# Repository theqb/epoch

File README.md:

# epoch
Open-source hardware + software lap-timer for racing

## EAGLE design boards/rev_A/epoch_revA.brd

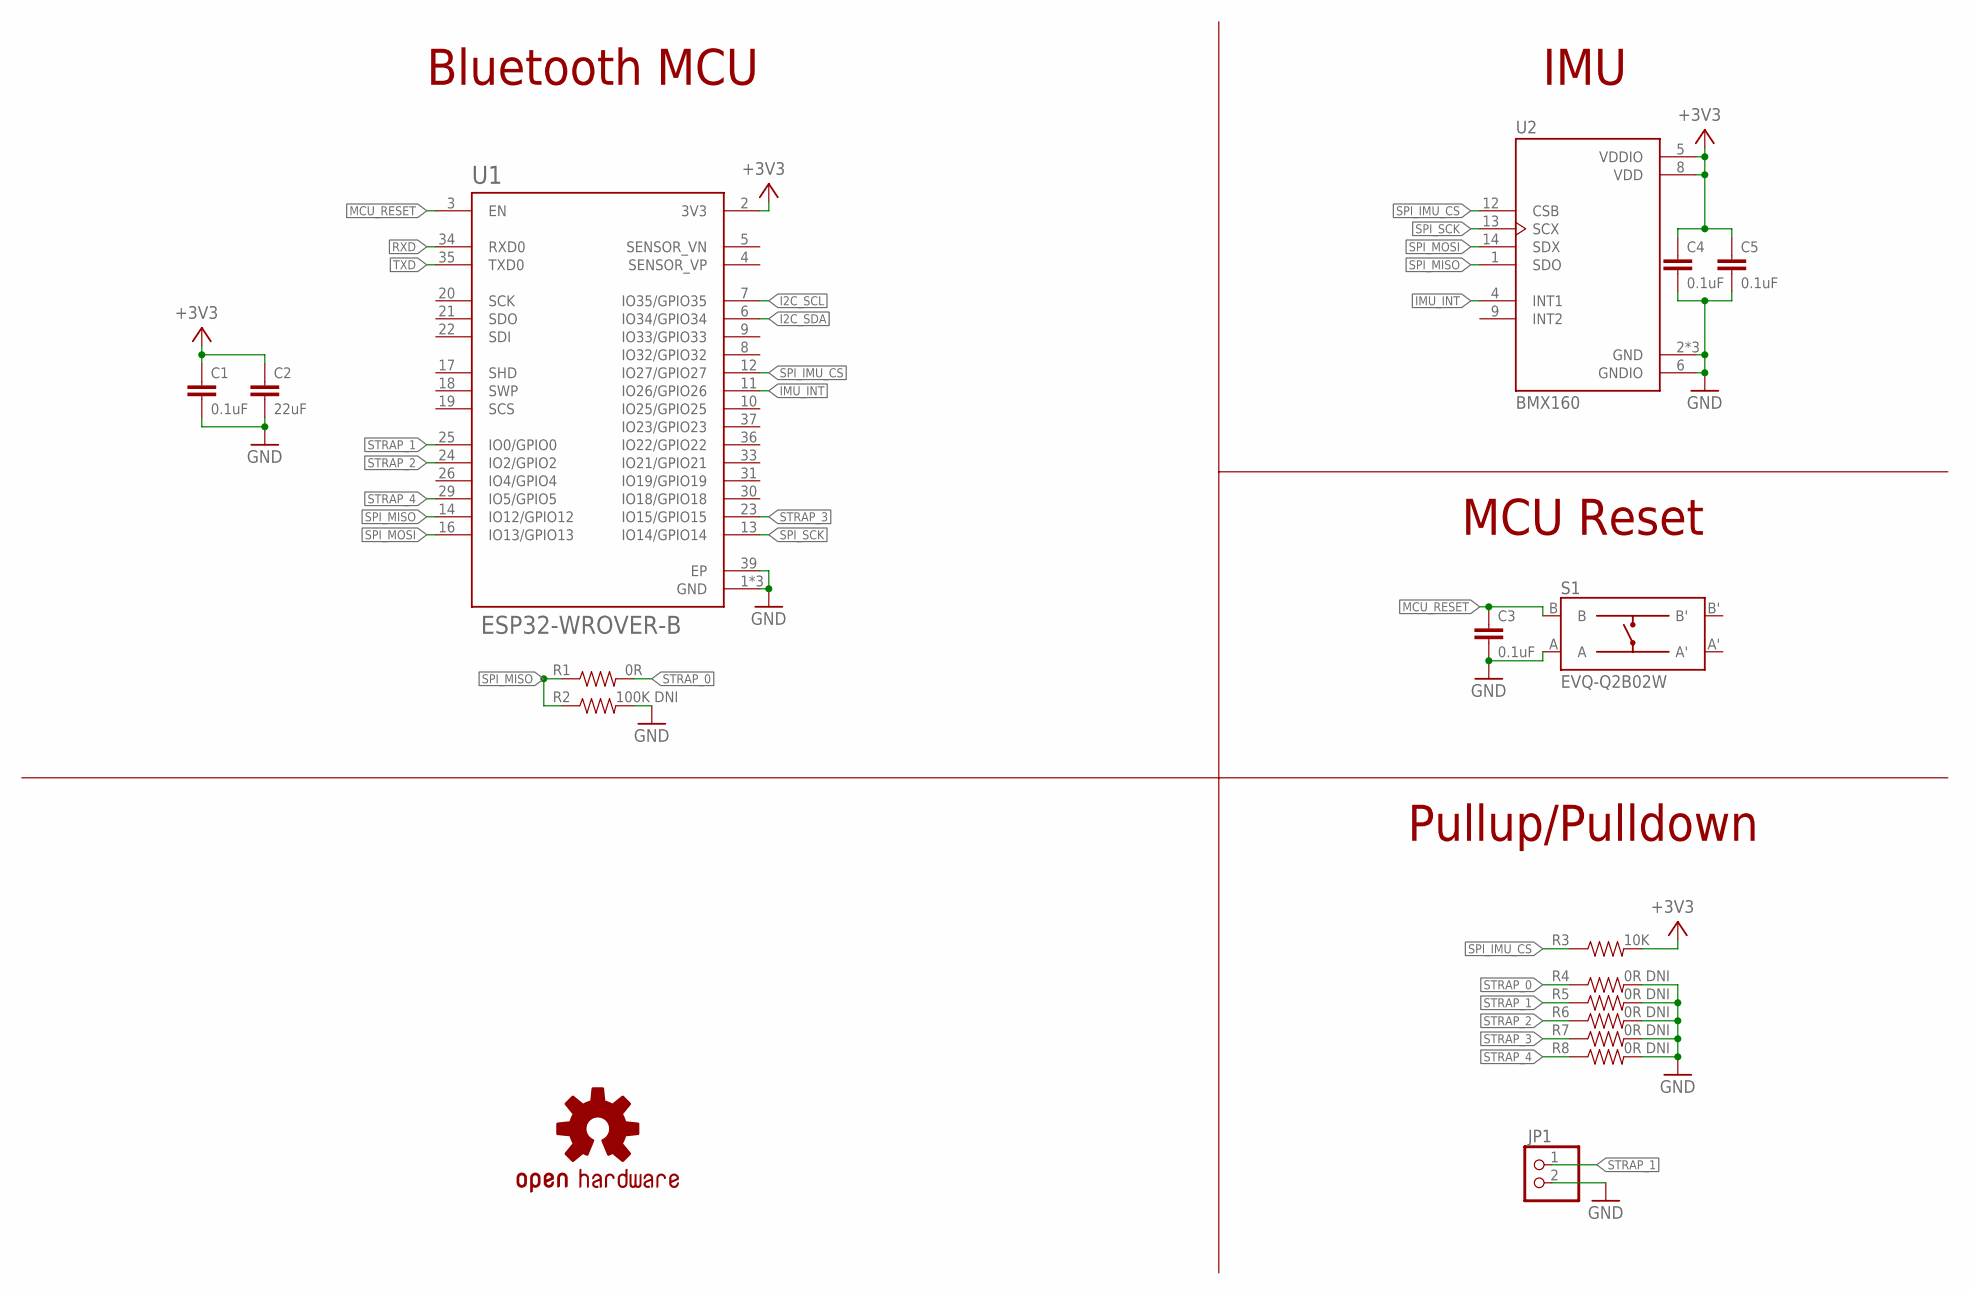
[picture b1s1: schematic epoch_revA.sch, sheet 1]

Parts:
C1, C3, C4, C5: 0.1uF; 0603
C2: 22uF; 0603
JP1: PINHD-1X2; 1X02
LOGO1: OSHW-LOGOMINI; OSHW-LOGO-MINI
R1: 0R; 0603
R2: 100K DNI; 0603
R3: 10K; 0603
R4, R5, R6, R7, R8: 0R DNI; 0603
S1: EVQ-Q2B02W; SW_EVQ-Q2B02W
U1: ESP32-WROVER-B; XCVR_ESP32-WROVER-B_(16MB)
U2: BMX160; PQFN50P250X300X100-14N

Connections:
+3V3: C1.1, C2.1, C4.1, C5.1, R3.2, U1.2 (3V3), U2.5 (VDDIO), U2.8 (VDD); also elsewhere on the board
GND: C1.2, C2.2, C3.2, C4.2, C5.2, JP1.2, R2.2, R4.2, R5.2, R6.2, R7.2, R8.2, S1.A, U1.1 (GND), U1.15 (GND), U1.38 (GND), U1.39 (EP), U2.2 (GND), U2.3 (GND), U2.6 (GNDIO), U2.7 (GND); also elsewhere on the board
I2C_SCL: U1.7 (IO35/GPIO35); also elsewhere on the board
I2C_SDA: U1.6 (IO34/GPIO34); also elsewhere on the board
IMU_INT: U1.11 (IO26/GPIO26), U2.4 (INT1)
MCU_RESET: C3.1, S1.B, U1.3 (EN)
RXD: U1.34 (RXD0)
SPI_IMU_CS: R3.1, U1.12 (IO27/GPIO27), U2.12 (CSB)
SPI_MISO: R1.1, R2.1, U1.14 (IO12/GPIO12), U2.1 (SDO)
SPI_MOSI: U1.16 (IO13/GPIO13), U2.14 (SDX)
SPI_SCK: U1.13 (IO14/GPIO14), U2.13 (SCX)
STRAP_0: R1.2, R4.1
STRAP_1: JP1.1, R5.1, U1.25 (IO0/GPIO0)
STRAP_2: R6.1, U1.24 (IO2/GPIO2)
STRAP_3: R7.1, U1.23 (IO15/GPIO15)
STRAP_4: R8.1, U1.29 (IO5/GPIO5)
TXD: U1.35 (TXD0)

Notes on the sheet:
IMU
Pullup/Pulldown
Bluetooth MCU
MCU Reset

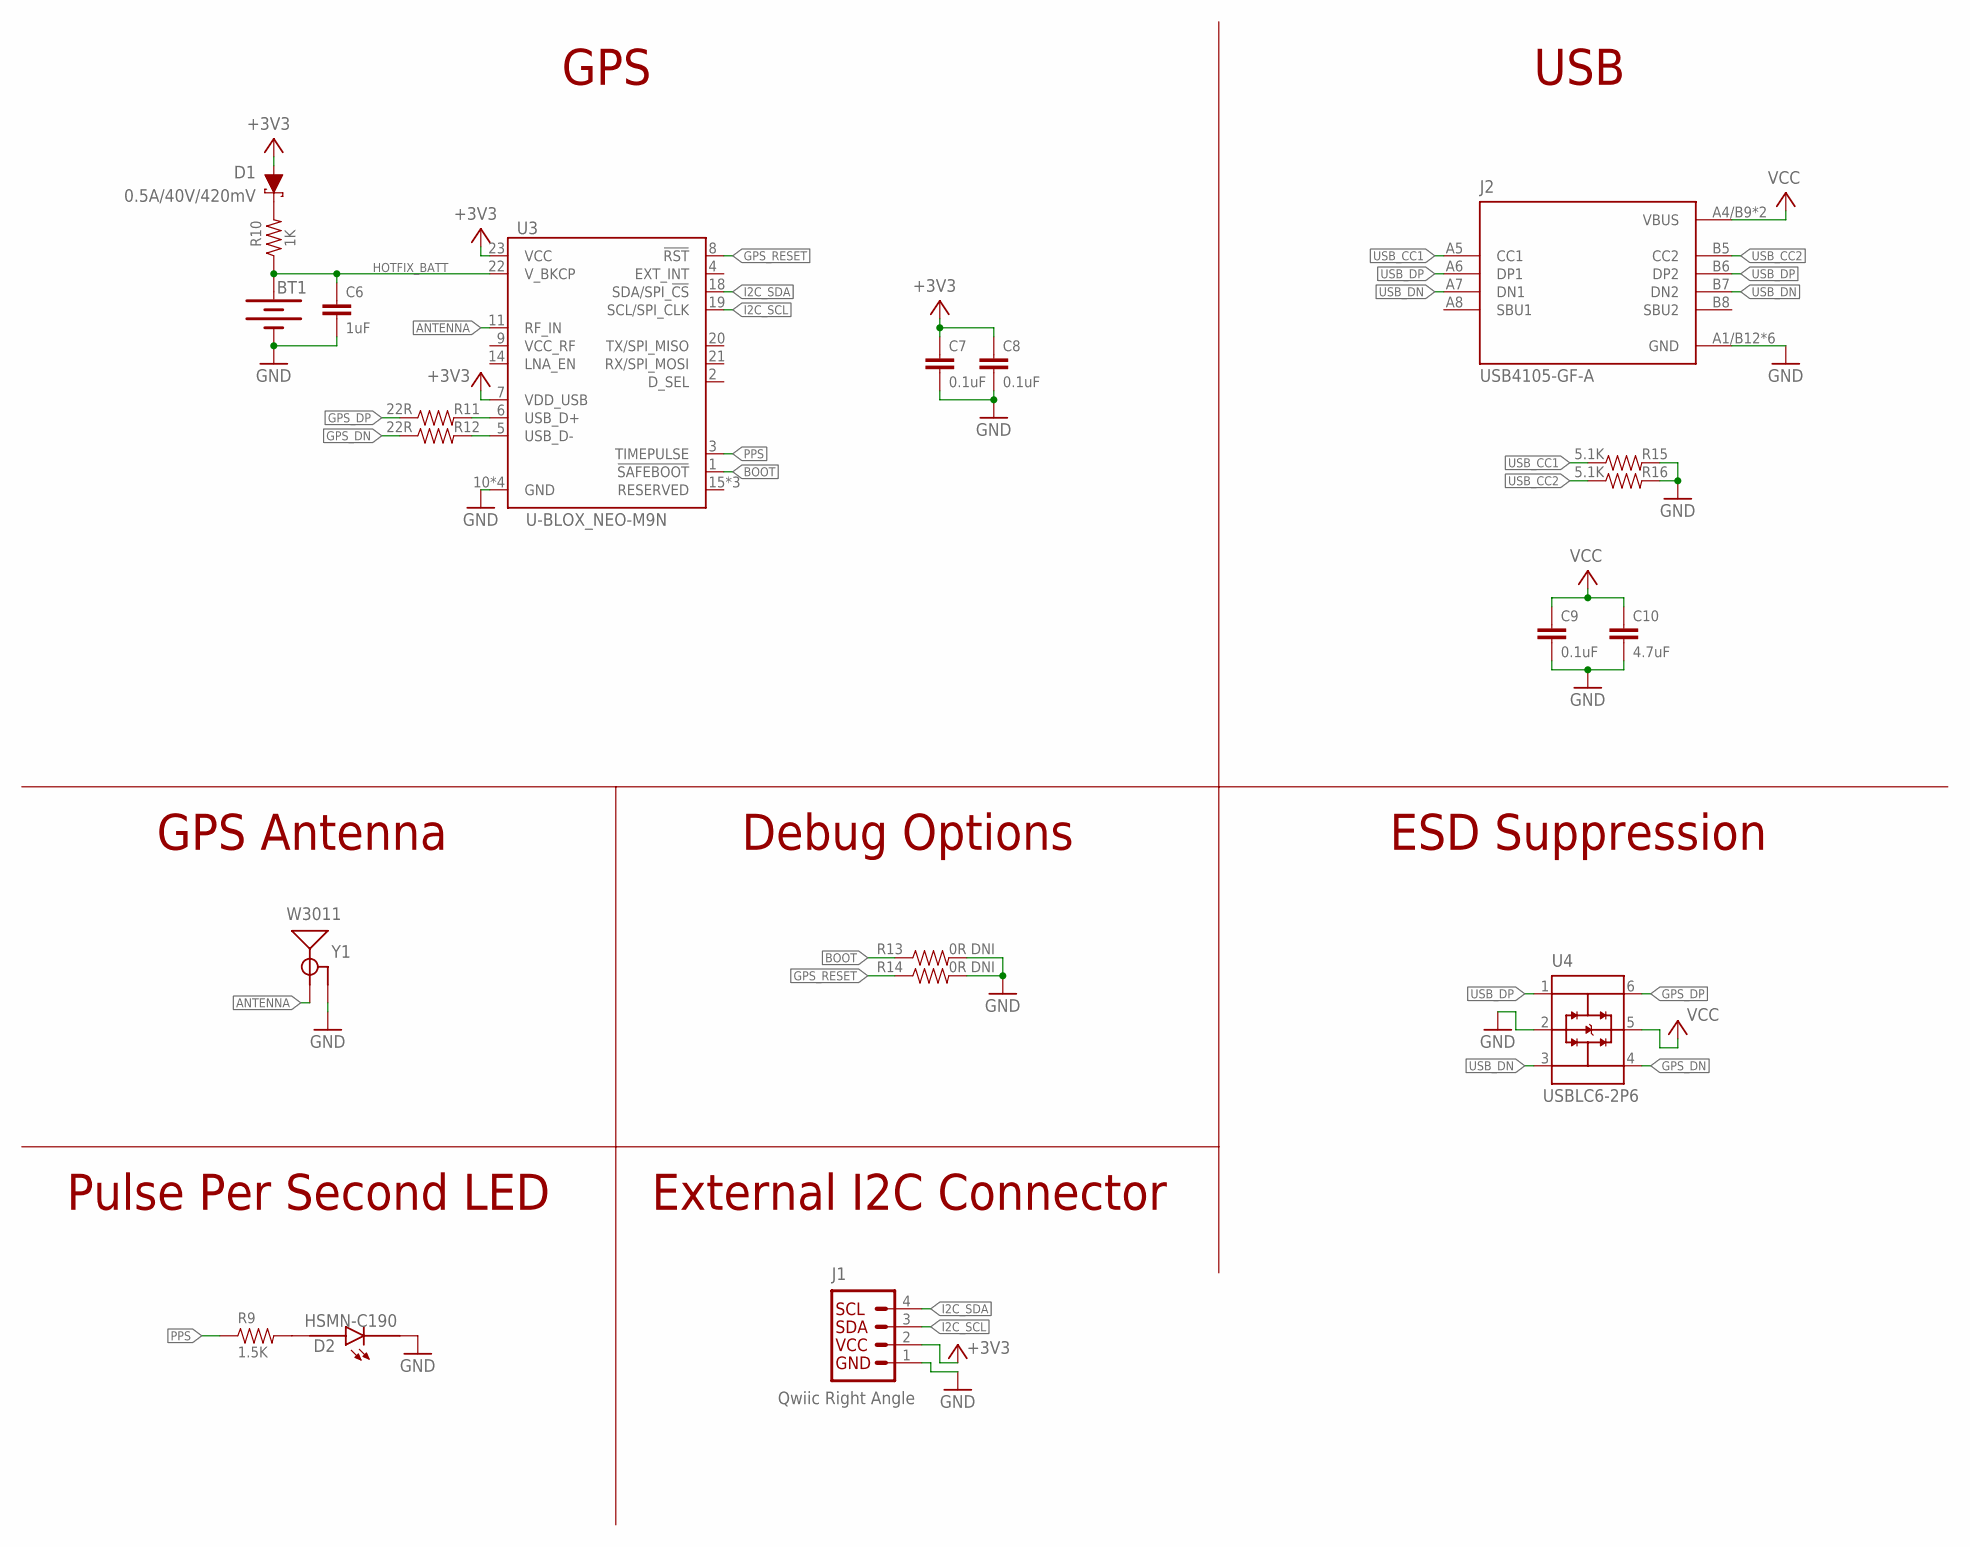
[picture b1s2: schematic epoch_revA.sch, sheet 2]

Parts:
BT1: ML414H-IV01E; ML414H_IV01E
C6: 1uF; 0603
C7, C8, C9: 0.1uF; 0603
C10: 4.7uF; 0603
D1: 0.5A/40V/420mV; SOD-323
D2: HSMN-C190; LEDM1608X80
J1: Qwiic Right Angle; 1X04_1MM_RA
J2: USB4105-GF-A; GCT_USB4105-GF-A
R9: 1.5K; 0603
R10: 1K; 0603
R11, R12: 22R; 0603
R13, R14: 0R DNI; 0603
R15, R16: 5.1K; 0603
U3: U-BLOX_NEO-M9N; NEO-M9N
U4: USBLC6-2P6; SOT50P160X60-6N
Y1: W3011

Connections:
+3V3: C7.1, C8.1, D1.A, J1.2, U3.7 (VDD_USB), U3.23 (VCC); also elsewhere on the board
ANTENNA: U3.11 (RF_IN), Y1.1 (SIGNAL)
BOOT: R13.1, U3.1 (!SAFEBOOT!)
DN: R12.2, U3.5 (USB_D-)
DP: R11.2, U3.6 (USB_D+)
GND: BT1.-, C6.2, C7.2, C8.2, C9.2, C10.2, D2.C, J1.1, J2.A1/B12 (GND), J2.B1/A12 (GND), J2.G1 (GND), J2.G2 (GND), J2.G3 (GND), J2.G4 (GND), R13.2, R14.2, R15.2, R16.2, U3.10 (GND), U3.12 (GND), U3.13 (GND), U3.24 (GND), U4.2 (GND), Y1.2 (GND), Y1.3 (GND); also elsewhere on the board
GPS_DN: R12.1, U4.4 (I/O2_2)
GPS_DP: R11.1, U4.6 (I/O1_2)
GPS_RESET: R14.1, U3.8 (!RST)
HOTFIX_BATT: BT1.+, C6.1, R10.1, U3.22 (V_BKCP)
I2C_SCL: J1.3, U3.19 (SCL/SPI_CLK); also elsewhere on the board
I2C_SDA: J1.4, U3.18 (SDA/SPI_!CS!); also elsewhere on the board
unnamed: D1.C, R10.2
unnamed: D2.A, R9.2
PPS: R9.1, U3.3 (TIMEPULSE)
USB_CC1: J2.A5 (CC1), R15.1
USB_CC2: J2.B5 (CC2), R16.1
USB_DN: J2.A7 (DN1), J2.B7 (DN2), U4.3 (I/O2_1)
USB_DP: J2.A6 (DP1), J2.B6 (DP2), U4.1 (I/O1_1)
VCC: C9.1, C10.1, J2.A4/B9 (VBUS), J2.B4/A9 (VBUS), U4.5 (VBUS); also elsewhere on the board

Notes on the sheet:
GPS
USB
ESD Suppression
GPS Antenna
Debug Options
Pulse Per Second LED
External I2C Connector

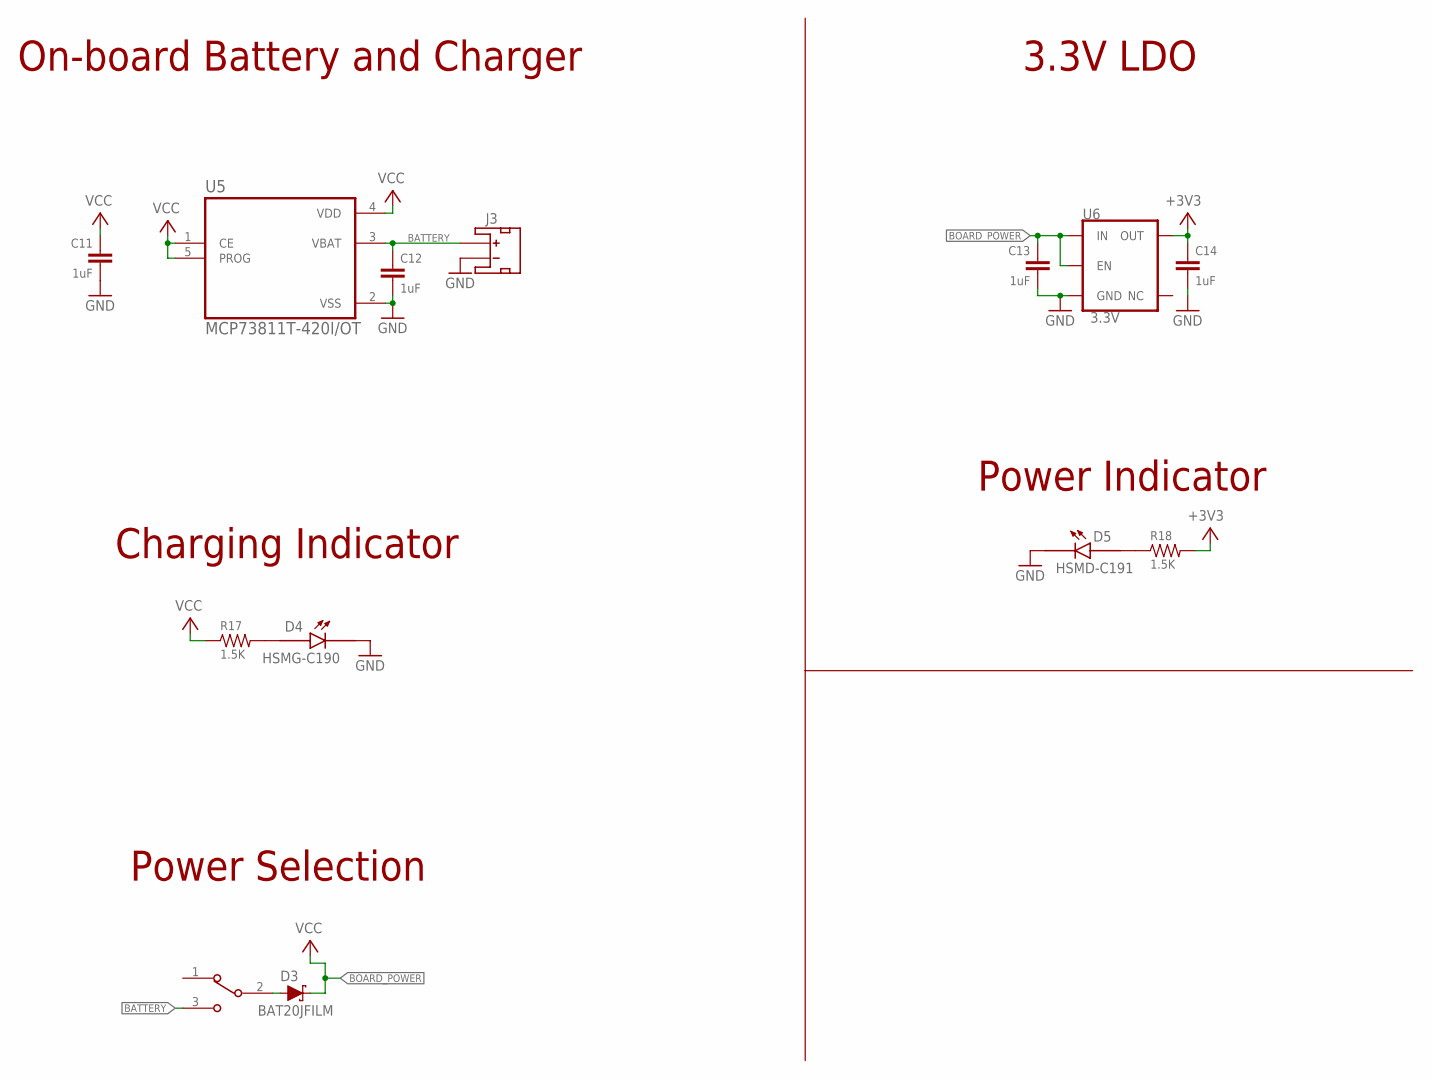
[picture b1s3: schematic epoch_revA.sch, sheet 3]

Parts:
C11, C12, C13, C14: 1uF; 0603
D3: BAT20JFILM; SOD-323
D4: HSMG-C190; LEDM1608X80
D5: HSMD-C191; LEDM1608X80
J3: JST_2MM_MALE; JST-2-SMD
R17, R18: 1.5K; 0603
S2: EG1213; SW_EG1213
U5: MCP73811T-420I/OT; SOT95P280X145-5N
U6: 3.3V; SOT23-5

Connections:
+3V3: C14.1, R18.2, U6.5 (OUT); also elsewhere on the board
BATTERY: C12.1, J3.2 (+), S2.3, U5.3 (VBAT)
BOARD_POWER: C13.1, D3.C, U6.1 (IN), U6.3 (EN)
GND: C11.2, C12.2, C13.2, C14.2, D4.C, D5.C, J3.1 (-), U5.2 (VSS), U6.2 (GND); also elsewhere on the board
unnamed: D5.A, R18.1
unnamed: D4.A, R17.2
unnamed: D3.A, S2.2
VCC: C11.1, R17.1, U5.1 (CE), U5.4 (VDD), U5.5 (PROG); also elsewhere on the board

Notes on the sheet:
3.3V LDO
On-board Battery and Charger
Charging Indicator
Power Indicator
Power Selection

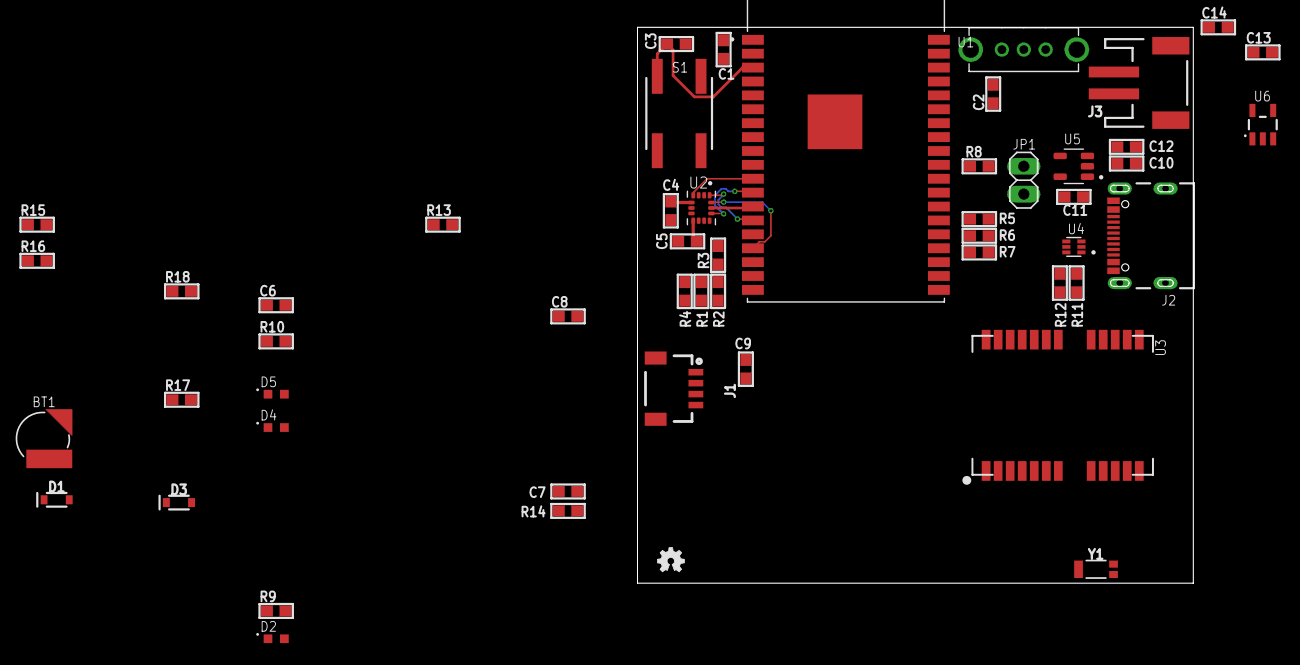
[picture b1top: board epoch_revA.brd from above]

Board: 2 copper layers, 50.8 x 50.8 mm, 52 parts (0 on the bottom side), 36 nets.

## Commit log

2020-01-28 added some base board files
2020-01-28 started defining board outline
2020-01-28 working on pin connections
2020-01-28 deleted extra page
2020-02-07 added rf components
2020-02-09 finished schematic
2020-02-09 working on layout
2020-02-10 working on rough layout
2020-02-10 added pdf

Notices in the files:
parts and their libraries:
SparkFun-Connectors: Licensing: Creative Commons ShareAlike 4.0 International - https://creativecommons.org/licenses/by-sa/4.0
